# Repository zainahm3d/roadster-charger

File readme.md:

# Roadster Charger
This project is a 65W USB-PD charger for a 36V (nominal) ebike battery. It is designed as a constant current -> constant voltage charger for the Ride1Up Roadster v2 bike.

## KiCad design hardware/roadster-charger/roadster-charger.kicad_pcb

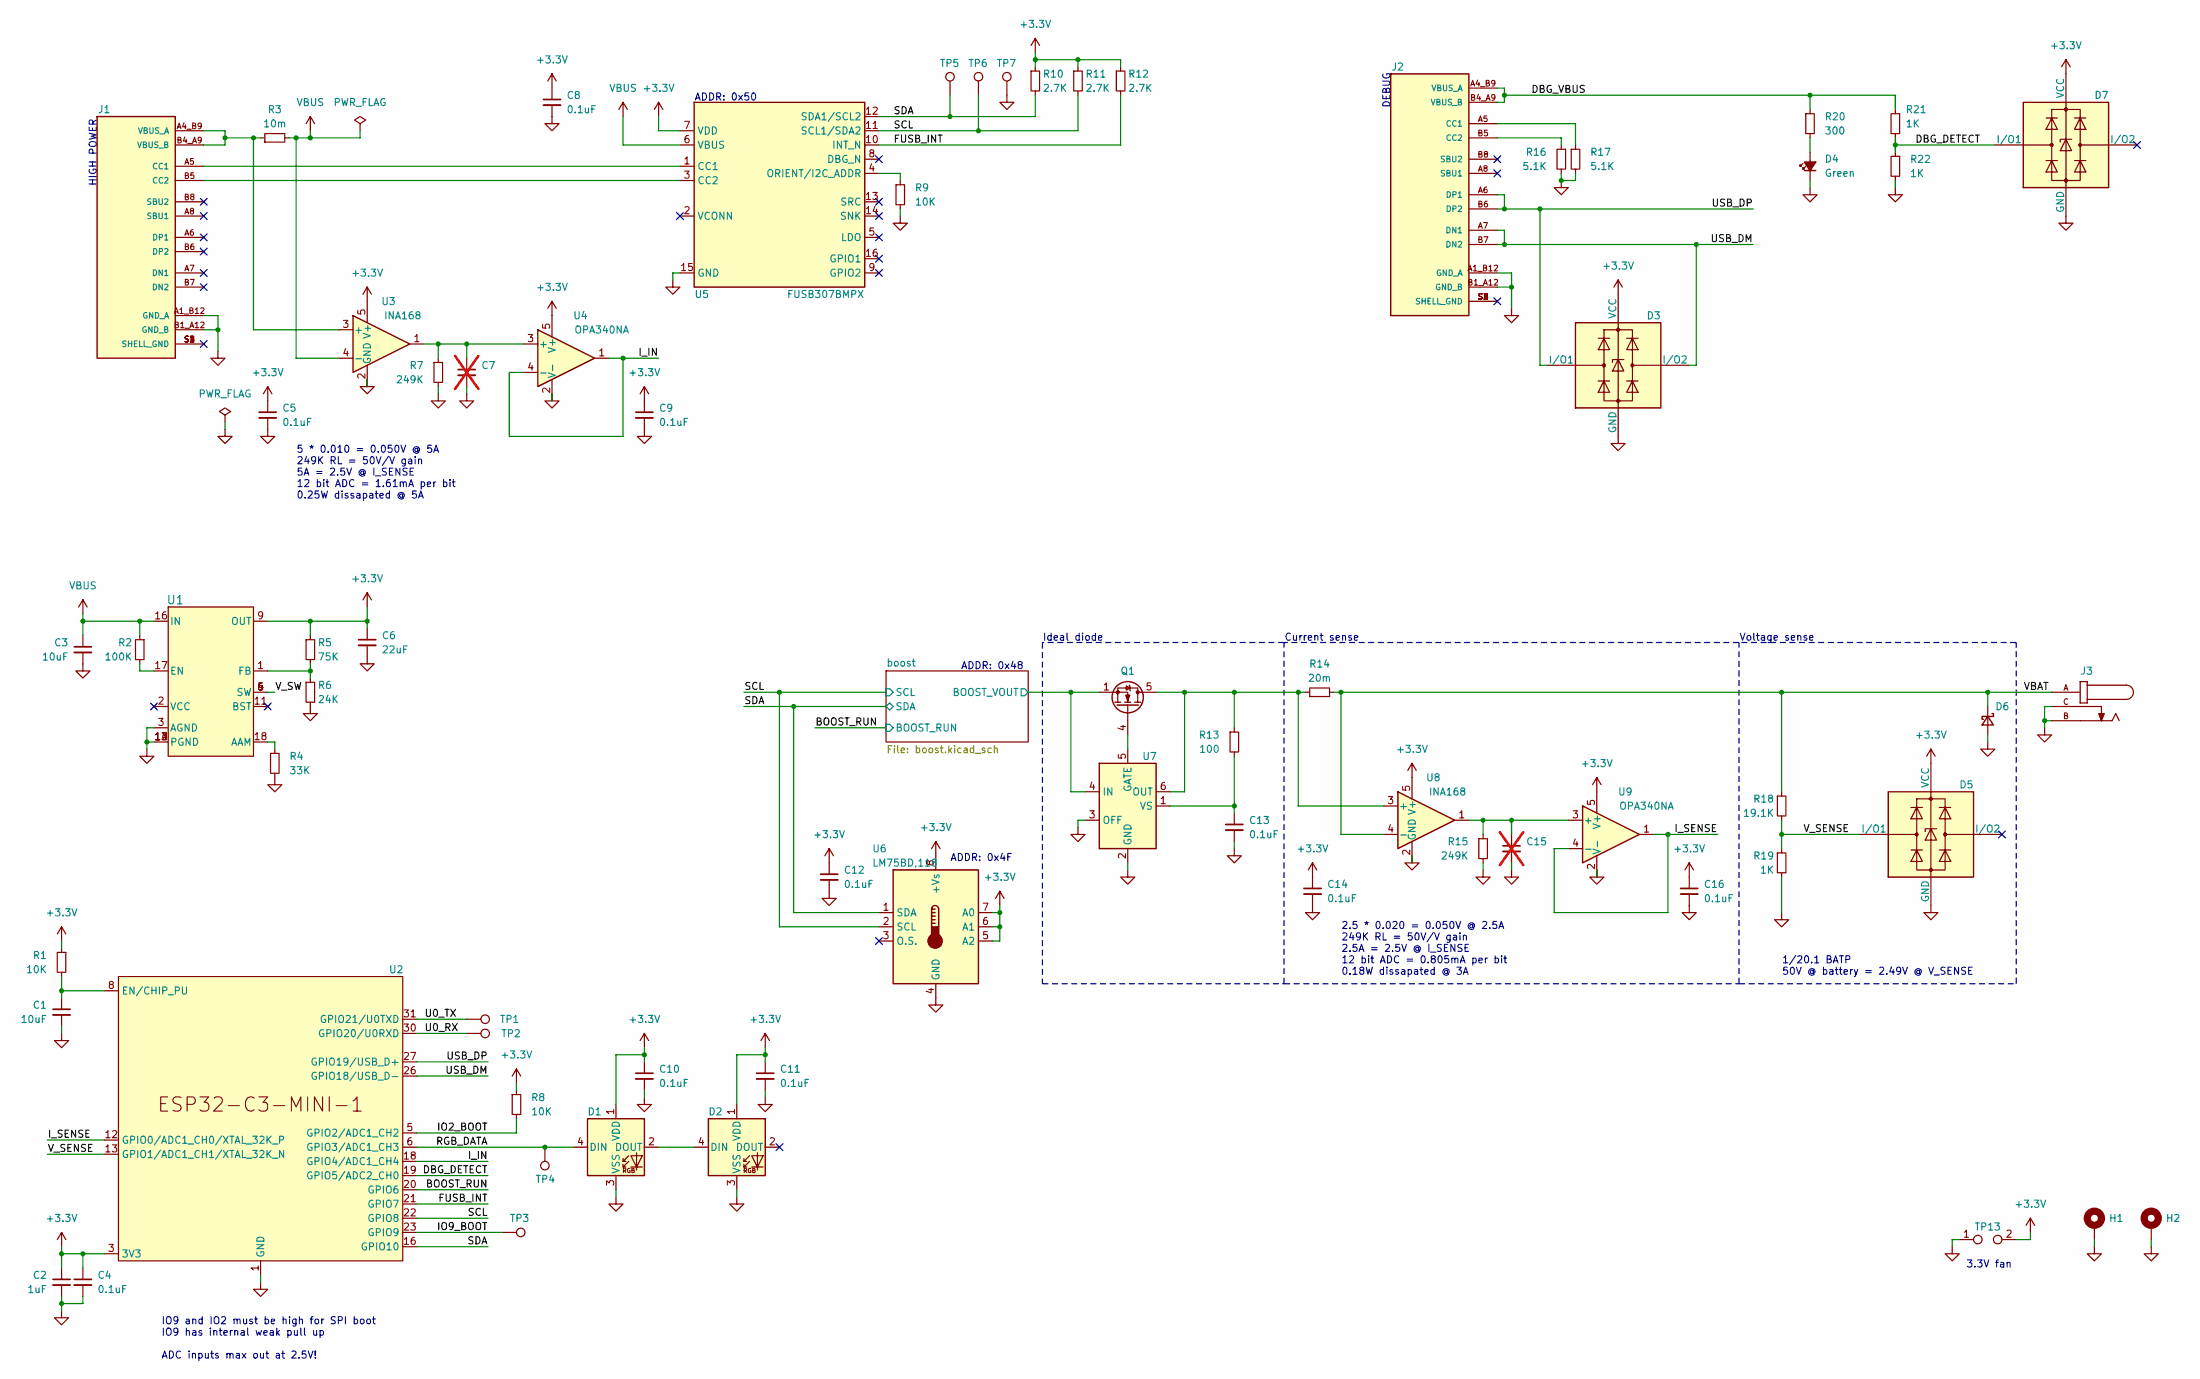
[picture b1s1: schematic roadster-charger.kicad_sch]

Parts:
C1, C3: 10uF; C_1206_3216Metric; MPN CL31A106MBHNNNE
C2: 1uF; C_0805_2012Metric; MPN CL21B105KAFNNNE
C4, C5, C8, C9, C10, C11, C12, C14, C16: 0.1uF; C_0603_1608Metric; MPN CL10B104KB8NNNC
C6: 22uF; C_1206_3216Metric; MPN CL31A226KAHNNNE
C7, C15: C_0603_1608Metric; MPN DNP; not fitted
C13: 0.1uF; C_0603_1608Metric; MPN CL10B104KC8NNNC
D1, D2: WS2812B; LED_WS2812B_PLCC4_5.0x5.0mm_P3.2mm; MPN COM-16347
D3, D5, D7: PRTR5V0U2X; SOT-143; MPN PRTR5V0U2X,215
D4: Green; LED_0805_2012Metric; MPN 150080VS75000
D6: D_Schottky_Small; D_SMB; MPN SMBJ60A
H1, H2: MountingHole_Pad; MountingHole_3.2mm_M3_ISO7380_Pad_TopBottom; MPN DNP
J1, J2: USB4505-03-0-A; GCT_USB4505-03-0-A_REVA; MPN USB4505-03-0-A
J3: 54-00166; TENSILITY_54-00166; MPN 54-00166
Q1: CSD19532Q5B; TDSON-8-1; MPN CSD19532Q5B
R1, R8, R9: 10K; R_0603_1608Metric; MPN RMCF0603FT10K0
R2: 100K; R_0603_1608Metric; MPN RC0603FR-07100KL
R3: 10m; R_1206_3216Metric; MPN PE1206FRF470R01L
R4: 33K; R_0603_1608Metric; MPN RMCF0603FT33K0
R5: 75K; R_0603_1608Metric; MPN RC0603FR-0775KL
R6: 24K; R_0603_1608Metric; MPN RC0603FR-1024KL
R7, R15: 249K; R_0603_1608Metric; MPN RMCF0603FT249K
R10, R11, R12: 2.7K; R_0603_1608Metric; MPN RC0603JR-072K7L
R13: 100; R_0603_1608Metric; MPN RMCF0603FT100R
R14: 20m; R_1206_3216Metric; MPN PA1206FRF470R02L
R16, R17: 5.1K; R_0603_1608Metric; MPN RC0603FR-075K1L
R18: 19.1K; R_0603_1608Metric; MPN RMCF0603FT19K1
R19, R21, R22: 1K; R_0603_1608Metric; MPN RT0603BRD071KL
R20: 300; R_0603_1608Metric; MPN RC0603JR-07330RL
TP1, TP2, TP3, TP4, TP5, TP6, TP7: RCU-0C; TP+195X110; MPN RCU-0C
TP13: TestPoint_2Pads_Pitch2.54mm_Drill0.8mm
U1: MPM3606AGQV-P; QFN3p0x5p0x1p6_MPM3606A_MNP; MPN MPM3606AGQV-P
U2: ESP32-C3-MINI-1; MPN ESP32-C3-MINI-1-N4
U3, U8: INA168; SOT-23-5; MPN INA168NA
U4, U9: OPA340NA; SOT-23-5; MPN OPA340NA
U5: FUSB307BMPX; WQFN-16-1EP_3x3mm_P0.5mm_EP1.75x1.75mm; MPN FUSB307BMPX
U6: LM75BD,118; SOIC-8_3.9x4.9mm_P1.27mm; MPN LM75BD,118
U7: LM5050-1; TSOT-23-6; MPN LM5050MKX-1/NOPB

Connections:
+3.3V: C2.1, C4.1, C5.1, C6.1, C8.1, C9.1, C10.1, C11.1, C12.1, C14.1, C16.1, D1.1 (VDD), D2.1 (VDD), D3.4 (VCC), D5.4 (VCC), D7.4 (VCC), R1.1, R5.1, R8.1, R10.1, R11.1, R12.1, TP13.2, U1.7 (OUT), U1.8 (OUT), U1.9 (OUT), U2.3 (3V3), U3.5 (V+), U4.5 (V+), U5.7 (VDD), U6.5 (A2), U6.6 (A1), U6.7 (A0), U6.8 (+Vs), U8.5 (V+), U9.5 (V+); also elsewhere on the board
/BOOST_RUN: U2.20 (GPIO6); also elsewhere on the board
/DBG_DETECT: D7.2 (I/O1), R21.2, R22.1, U2.19 (GPIO5/ADC2_CH0)
/DBG_VBUS: J2.A4_B9 (VBUS_A), J2.B4_A9 (VBUS_B), R20.1, R21.1
/FUSB_INT: R12.2, U2.21 (GPIO7), U5.10 (INT_N)
/IO2_BOOT: R8.2, U2.5 (GPIO2/ADC1_CH2)
/IO9_BOOT: TP3.1, U2.23 (GPIO9)
/I_IN: U2.18 (GPIO4/ADC1_CH4), U4.1, U4.4 (-)
/I_SENSE: U2.12 (GPIO0/ADC1_CH0/XTAL_32K_P), U9.1, U9.4 (-)
/RGB_DATA: D1.4 (DIN), TP4.1, U2.6 (GPIO3/ADC1_CH3)
/SCL: R11.2, TP6.1, U2.22 (GPIO8), U5.11 (SCL1/SDA2), U6.2 (SCL); also elsewhere on the board
/SDA: R10.2, TP5.1, U2.16 (GPIO10), U5.12 (SDA1/SCL2), U6.1 (SDA); also elsewhere on the board
/U0_RX: TP2.1, U2.30 (GPIO20/U0RXD)
/U0_TX: TP1.1, U2.31 (GPIO21/U0TXD)
/USB_DM: D3.3 (I/O2), J2.A7 (DN1), J2.B7 (DN2), U2.26 (GPIO18/USB_D-)
/USB_DP: D3.2 (I/O1), J2.A6 (DP1), J2.B6 (DP2), U2.27 (GPIO19/USB_D+)
/VBAT: D6.1 (K), J3.A, R14.2, R18.1, U8.4 (-)
/V_SENSE: D5.2 (I/O1), R18.2, R19.1, U2.13 (GPIO1/ADC1_CH1/XTAL_32K_N)
/V_SW: U1.4 (SW), U1.5 (SW), U1.6 (SW)
/boost/BOOST_VOUT: Q1.1 (S), Q1.2 (S), Q1.3 (S), U7.4 (IN); also elsewhere on the board
GND: C1.2, C2.2, C3.2, C4.2, C5.2, C6.2, C7.2, C8.2, C9.2, C10.2, C11.2, C12.2, C13.2, C14.2, C15.2, C16.2, D1.3 (VSS), D2.3 (VSS), D3.1 (GND), D4.1 (K), D5.1 (GND), D6.2 (A), D7.1 (GND), H1.1, H2.1, J1.A1_B12 (GND_A), J1.B1_A12 (GND_B), J2.A1_B12 (GND_A), J2.B1_A12 (GND_B), J3.B, J3.C, R4.2, R6.2, R7.2, R9.2, R15.2, R16.2, R17.2, R19.2, R22.2, TP7.1, TP13.1, U1.3 (AGND), U1.12 (PGND), U1.13 (PGND), U1.14 (PGND), U2.1 (GND), U2.2 (GND), U2.11 (GND), U2.14 (GND), U2.36 (GND), U2.37 (GND), U2.38 (GND), U2.39 (GND), U2.40 (GND), U2.41 (GND), U2.42 (GND), U2.43 (GND), U2.44 (GND), U2.45 (GND), U2.46 (GND), U2.47 (GND), U2.48 (GND), U2.49 (GND), U2.50 (GND), U2.51 (GND), U2.52 (GND), U2.53 (GND), U3.2 (GND), U4.2 (V-), U5.15 (GND), U5.17 (GND), U6.4 (GND), U7.2 (GND), U7.3 (OFF), U8.2 (GND), U9.2 (V-); also elsewhere on the board
unnamed: D1.2 (DOUT), D2.4 (DIN)
unnamed: D4.2 (A), R20.2
unnamed: J1.A5 (CC1), U5.1 (CC1)
unnamed: J1.B5 (CC2), U5.3 (CC2)
unnamed: J1.A4_B9 (VBUS_A), J1.B4_A9 (VBUS_B), R3.1, U3.3 (+)
unnamed: J2.A5 (CC1), R17.1
unnamed: J2.B5 (CC2), R16.1
unnamed: Q1.5 (D), R13.1, R14.1, U7.6 (OUT), U8.3 (+)
unnamed: Q1.4 (G), U7.5 (GATE)
unnamed: R4.1, U1.18 (AAM)
unnamed: R2.2, U1.17 (EN)
unnamed: R5.2, R6.1, U1.1 (FB)
unnamed: C1.1, R1.2, U2.8 (EN/CHIP_PU)
unnamed: C7.1, R7.1, U3.1, U4.3 (+)
unnamed: R9.1, U5.4 (ORIENT/I2C_ADDR)
unnamed: C13.1, R13.2, U7.1 (VS)
unnamed: C15.1, R15.1, U8.1, U9.3 (+)
VBUS: C3.1, R2.1, R3.2, U1.16 (IN), U3.4 (-), U5.6 (VBUS); also elsewhere on the board

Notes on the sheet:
ADDR: 0x50
5 * 0.010 = 0.050V @ 5A 249K RL = 50V/V gain 5A = 2.5V @ I_SENSE 12 bit ADC = 1.61mA per bit 0.25W dissapated @ 5A
3.3V fan
Ideal diode
1/20.1 BATP 50V @ battery = 2.49V @ V_SENSE
DEBUG
HIGH POWER
Current sense
IO9 and IO2 must be high for SPI boot IO9 has internal weak pull up ADC inputs max out at 2.5V!
ADDR: 0x48
ADDR: 0x4F
Voltage sense
2.5 * 0.020 = 0.050V @ 2.5A 249K RL = 50V/V gain 2.5A = 2.5V @ I_SENSE 12 bit ADC = 0.805mA per bit 0.18W dissapated @ 3A

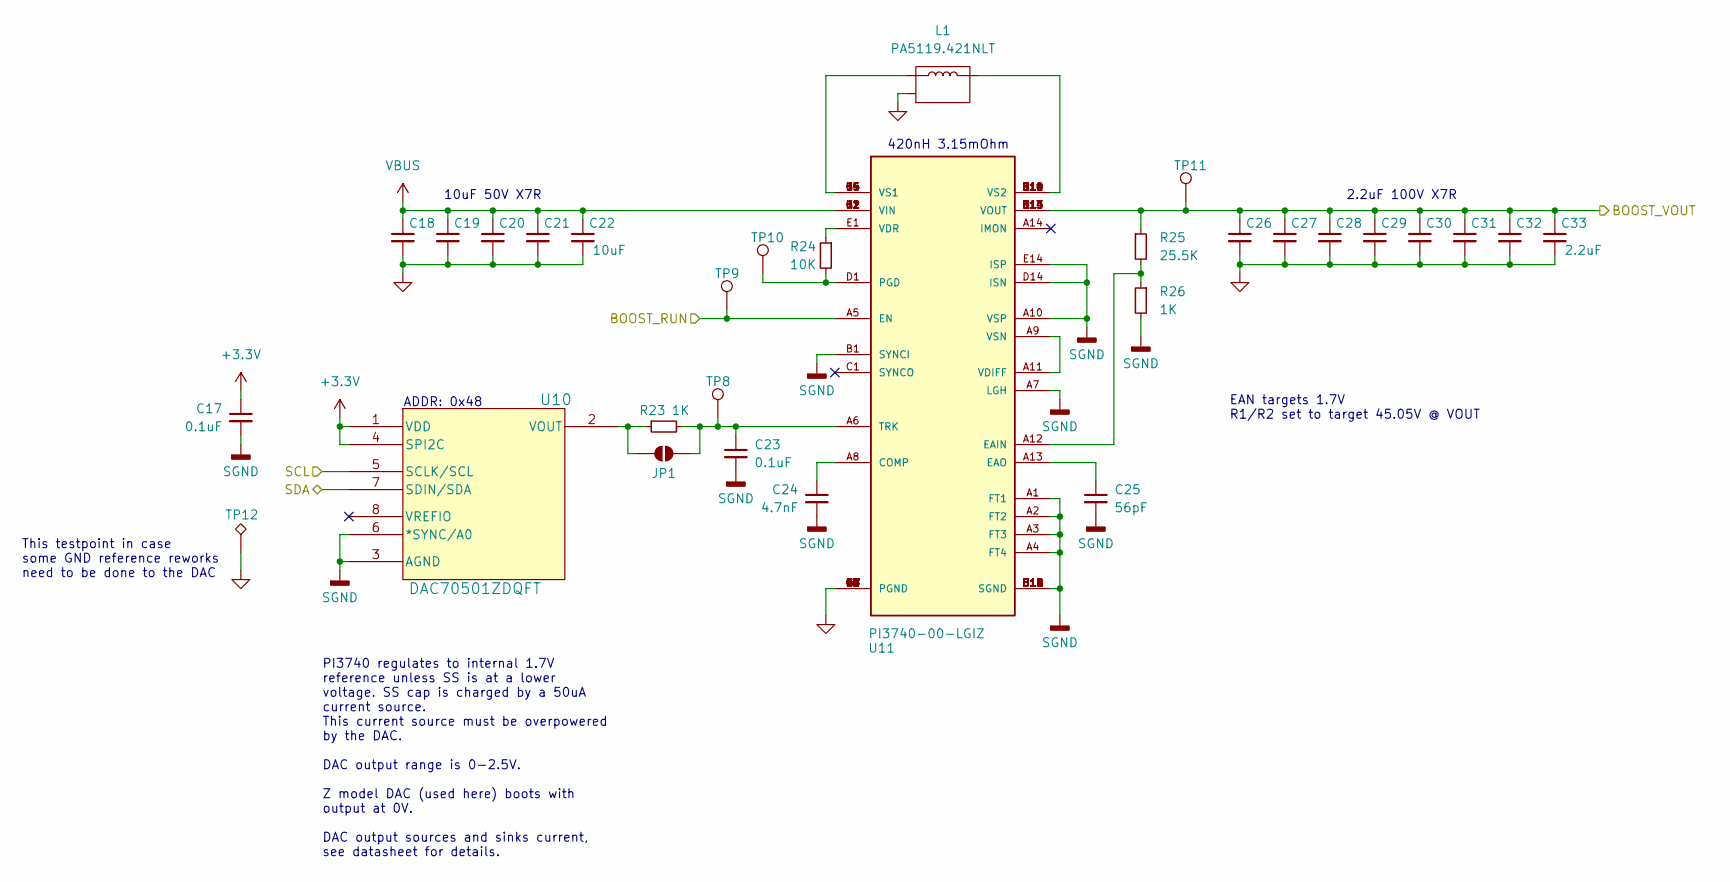
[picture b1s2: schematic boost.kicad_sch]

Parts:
C17, C23: 0.1uF; C_0603_1608Metric; MPN CL10B104KB8NNNC
C18, C19, C20, C21, C22: 10uF; C_1210_3225Metric; MPN CL32B106KBVVPLE
C24: 4.7nF; C_0603_1608Metric; MPN C0603C472K4RECAUTO7411
C25: 56pF; C_0603_1608Metric; MPN C0603C560G5GAC7867
C26, C27, C28, C29, C30, C31, C32, C33: 2.2uF; C_1210_3225Metric; MPN GRM32ER72A225KA35L
JP1: SolderJumper_2_Open; SolderJumper-2_P1.3mm_Open_RoundedPad1.0x1.5mm; MPN DNP
L1: PA5119.421NLT; SMT_119.421NLT_PUL; MPN PA5119.421NLT
R23, R26: 1K; R_0603_1608Metric; MPN RT0603BRD071KL
R24: 10K; R_0603_1608Metric; MPN RMCF0603FT10K0
R25: 25.5K; R_0603_1608Metric; MPN RT0603BRD0725K5L
TP8, TP9, TP10, TP11: RCU-0C; TP+195X110; MPN RCU-0C
TP12: TestPoint_Alt; TestPoint_THTPad_D1.0mm_Drill0.5mm; MPN DNP
U10: DAC70501ZDQFT; WSON8_2P1X2P1_TEX; MPN DAC70501ZDQFT
U11: PI3740-00-LGIZ; LGA108S100P10X14_1000X1400X263N; MPN PI3740-00-LGIZ

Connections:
+3.3V: C17.1, U10.1 (VDD), U10.4 (SPI2C); also elsewhere on the board
/BOOST_RUN: TP9.1, U11.A5 (EN); also elsewhere on the board
/SCL: U10.5 (SCLK/SCL); also elsewhere on the board
/SDA: U10.7 (SDIN/SDA); also elsewhere on the board
/boost/BOOST_VOUT: C26.1, C27.1, C28.1, C29.1, C30.1, C31.1, C32.1, C33.1, R25.1, TP11.1, U11.G13 (VOUT), U11.G14 (VOUT), U11.H13 (VOUT), U11.H14 (VOUT), U11.J13 (VOUT), U11.J14 (VOUT), U11.K13 (VOUT), U11.K14 (VOUT); also elsewhere on the board
GND: C18.2, C19.2, C20.2, C21.2, C22.2, C26.2, C27.2, C28.2, C29.2, C30.2, C31.2, C32.2, C33.2, L1.3 (MNT), TP12.1, U11.B2 (PGND), U11.B3 (PGND), U11.B4 (PGND), U11.B5 (PGND), U11.B6 (PGND), U11.B7 (PGND), U11.B8 (PGND), U11.B9 (PGND), U11.C2 (PGND), U11.C3 (PGND), U11.C4 (PGND), U11.C5 (PGND), U11.C6 (PGND), U11.C7 (PGND), U11.C8 (PGND), U11.C9 (PGND), U11.D2 (PGND), U11.D3 (PGND), U11.D4 (PGND), U11.D5 (PGND), U11.D6 (PGND), U11.D7 (PGND), U11.D8 (PGND), U11.D9 (PGND), U11.E2 (PGND), U11.E3 (PGND), U11.E4 (PGND), U11.E5 (PGND), U11.E6 (PGND), U11.E7 (PGND), U11.E8 (PGND), U11.E9 (PGND), U11.F7 (PGND), U11.F8 (PGND), U11.G7 (PGND), U11.G8 (PGND), U11.H7 (PGND), U11.H8 (PGND), U11.J7 (PGND), U11.J8 (PGND), U11.K7 (PGND), U11.K8 (PGND); also elsewhere on the board
unnamed: C23.1, JP1.1 (A), R23.2, TP8.1, U11.A6 (TRK)
unnamed: JP1.2 (B), R23.1, U10.2 (VOUT)
unnamed: L1.1, U11.G10 (VS2), U11.G11 (VS2), U11.H10 (VS2), U11.H11 (VS2), U11.J10 (VS2), U11.J11 (VS2), U11.K10 (VS2), U11.K11 (VS2)
unnamed: L1.2, U11.G4 (VS1), U11.G5 (VS1), U11.H4 (VS1), U11.H5 (VS1), U11.J4 (VS1), U11.J5 (VS1), U11.K4 (VS1), U11.K5 (VS1)
unnamed: C24.1, U11.A8 (COMP)
unnamed: R25.2, R26.1, U11.A12 (EAIN)
unnamed: C25.1, U11.A13 (EAO)
unnamed: R24.2, TP10.1, U11.D1 (PGD)
unnamed: U11.A9 (VSN), U11.A11 (VDIFF)
unnamed: R24.1, U11.E1 (VDR)
SGND: C17.2, C23.2, C24.2, C25.2, R26.2, U10.3 (AGND), U10.6 (*SYNC/A0), U11.A1 (FT1), U11.A2 (FT2), U11.A3 (FT3), U11.A4 (FT4), U11.A7 (LGH), U11.A10 (VSP), U11.B1 (SYNCI), U11.B10 (SGND), U11.B11 (SGND), U11.B12 (SGND), U11.B13 (SGND), U11.B14 (SGND), U11.C10 (SGND), U11.C11 (SGND), U11.C12 (SGND), U11.D10 (SGND), U11.D11 (SGND), U11.D12 (SGND), U11.D14 (ISN), U11.E10 (SGND), U11.E11 (SGND), U11.E12 (SGND), U11.E14 (ISP)
VBUS: C18.1, C19.1, C20.1, C21.1, C22.1, U11.G1 (VIN), U11.G2 (VIN), U11.H1 (VIN), U11.H2 (VIN), U11.J1 (VIN), U11.J2 (VIN), U11.K1 (VIN), U11.K2 (VIN); also elsewhere on the board

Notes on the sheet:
EAN targets 1.7V R1/R2 set to target 45.05V @ VOUT
ADDR: 0x48
This testpoint in case some GND reference reworks need to be done to the DAC
2.2uF 100V X7R
10uF 50V X7R
420nH 3.15mOhm
PI3740 regulates to internal 1.7V reference unless SS is at a lower voltage. SS cap is charged by a 50uA current source. This current source must be overpowered by the DAC. DAC output range is 0-2.5V. Z model DAC (used here) boots with output at 0V. DAC output sources and sinks current, see datashe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

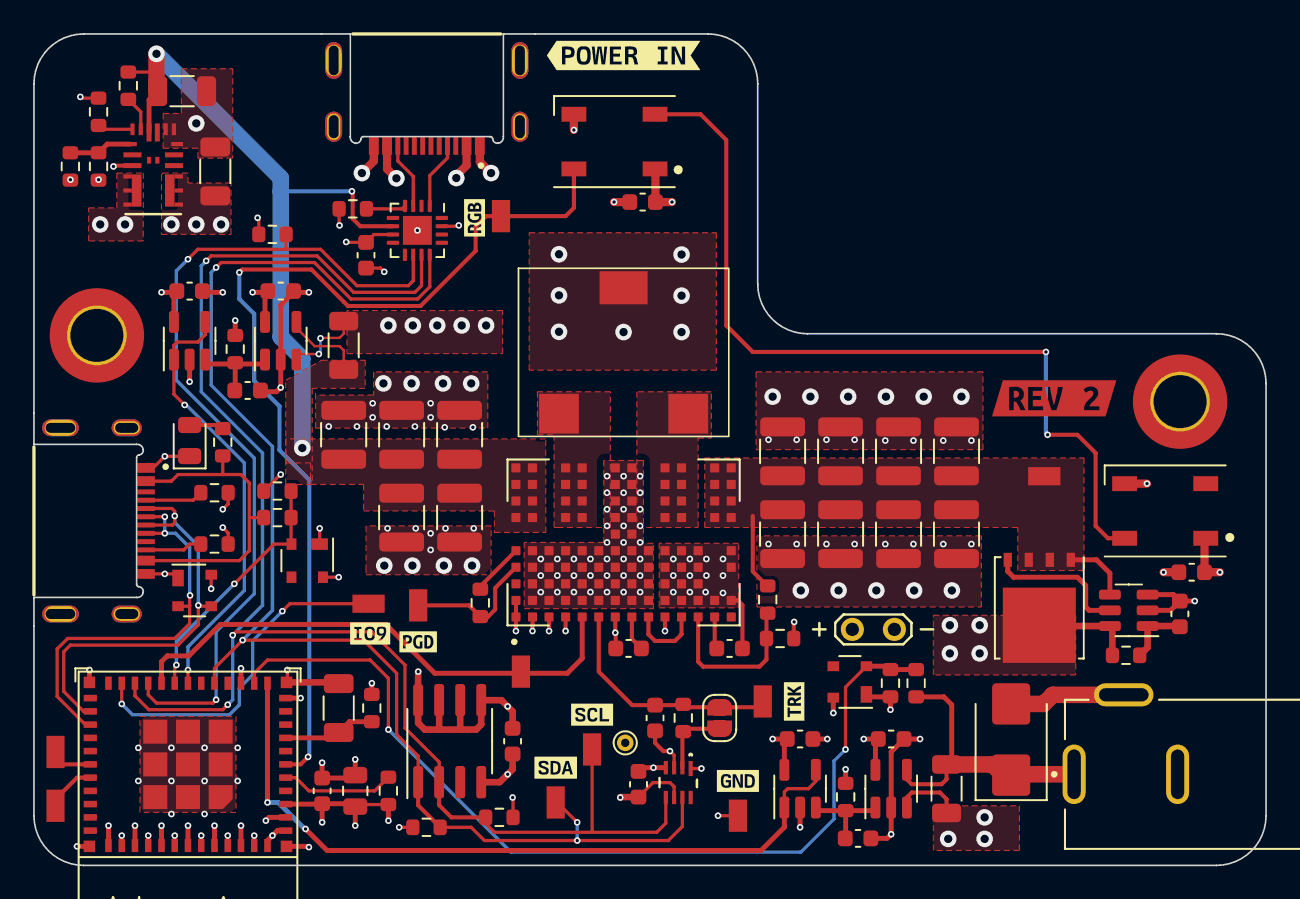
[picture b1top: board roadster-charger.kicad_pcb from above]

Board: 4 copper layers, 74.4 x 50.2 mm, 108 parts (0 on the bottom side), 50 nets.

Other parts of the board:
kibuzzard-657BAFF1: G***; kibuzzard-657BAFF1
kibuzzard-657BAFFB: G***; kibuzzard-657BAFFB
kibuzzard-657BB0E9: G***; kibuzzard-657BB0E9
kibuzzard-657BB005: G***; kibuzzard-657BB005
kibuzzard-657FB5DD: G***; kibuzzard-657FB5DD
kibuzzard-671EA982: G***; kibuzzard-671EA982
kibuzzard-671EA992: G***; kibuzzard-671EA992
kibuzzard-671EAE84: G***; kibuzzard-671EAE84
kibuzzard-671EB1B0: G***; kibuzzard-671EB1B0
kibuzzard-67218F63: G***; kibuzzard-67218F63

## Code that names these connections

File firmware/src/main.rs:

#![no_std]
#![no_main]

use core::sync::atomic::Ordering;
use esp_backtrace as _;
use esp_hal::{
    analog::adc::*,
    delay::Delay,
    gpio::{self, Input, InputConfig, Level, Output, OutputConfig},
    i2c, rtc_cntl,
    time::{Duration, Rate},
    timer::{
        timg::{MwdtStage, MwdtStageAction, TimerGroup, Wdt},
        PeriodicTimer,
    },
    Blocking,
};
use esp_println::println;

esp_bootloader_esp_idf::esp_app_desc!();

use crate::led::color;
mod boost;
mod charger;
mod led;
mod tcpc;
mod temp_sense;
mod usb_pd;
mod vi_sense;

#[rtic::app(device = esp32c3, dispatchers=[FROM_CPU_INTR0, FROM_CPU_INTR1])]
mod app {
    use crate::vi_sense::VISense;

    use super::*;

    #[shared]
    struct Shared {
        i2c: i2c::master::I2c<'static, Blocking>,
    }

    #[local]
    struct Local {
        fusb_int: gpio::Input<'static>,
        periodic: PeriodicTimer<'static, Blocking>,
        boost_enable: gpio::Output<'static>,
        vi_sense: VISense,
        state: shared::state::State,
        leds: led::Led,
        watchdog: Wdt<esp_hal::peripherals::TIMG0<'static>>,
    }

    #[init]
    fn init(_: init::Context) -> (Shared, Local) {
        let peripherals = esp_hal::init(esp_hal::Config::default());
        let mut delay = Delay::new();

        let i2c_config = i2c::master::Config::default().with_frequency(Rate::from_khz(400));
        let mut i2c = i2c::master::I2c::new(peripherals.I2C0, i2c_config)
            .unwrap()
            .with_scl(peripherals.GPIO8)
            .with_sda(peripherals.GPIO10);

        let rmt = esp_hal::rmt::Rmt::new(peripherals.RMT, Rate::from_mhz(80)).unwrap();
        let rmt_output = Output::new(peripherals.GPIO3, Level::Low, Default::default());
        let mut leds = led::Led {
            pixel_buffer: [led::Rgb { r: 0, g: 0, b: 0 }; 2],
            rmt_channel: Some(led::Led::configure_rmt(rmt, rmt_output)),
            last_update_time: esp_hal::time::Instant::EPOCH,
        };

        let mut adc1_config = AdcConfig::new();
        let vi_sense = VISense {
            v_sense: adc1_config.enable_pin_with_cal(peripherals.GPIO1, Attenuation::_11dB),
            i_sense: adc1_config.enable_pin_with_cal(peripherals.GPIO0, Attenuation::_11dB),
            input_i_sense: adc1_config.enable_pin_with_cal(peripherals.GPIO4, Attenuation::_11dB),
            adc: Adc::new(peripherals.ADC1, adc1_config),
            input_current_ma: 0,
            output_current_ma: 0,
            battery_voltage_mv: 0,
        };

        let mut boost_enable = Output::new(peripherals.GPIO6, Level::Low, OutputConfig::default());
        let mut fusb_int = Input::new(peripherals.GPIO7, InputConfig::default());

        boost::init(&mut i2c, &mut boost_enable);
        tcpc::init(&mut i2c, &mut delay);

        let reset_reason = rtc_cntl::reset_reason(esp_hal::system::Cpu::ProCpu);
        if let Some(reason) = reset_reason {
            if reason == rtc_cntl::SocResetReason::CoreMwdt0 {
                println!("System reset was due to watchdog");
                leds.set_pixel(0, color::PURPLE);
                leds.set_pixel(1, color::PURPLE);

                #[allow(clippy::empty_loop)]
                loop {}
            }
        }

        if tcpc::establish_pd_contract(&mut i2c, &mut fusb_int, &mut delay) {
            leds.set_pixel(0, color::GREEN);
        } else {
            leds.set_pixel(0, color::RED);
            panic!("failed to establish PD contract");
        }
        leds.set_pixel(1, color::RED);

        let timg0 = TimerGroup::new(peripherals.TIMG0);
        let mut watchdog = timg0.wdt;
        watchdog.set_stage_action(MwdtStage::Stage3, MwdtStageAction::ResetSystem);
        watchdog.set_timeout(MwdtStage::Stage3, Duration::from_secs(2));
        watchdog.enable();

        let mut periodic = PeriodicTimer::new(timg0.timer0);
        periodic.enable_interrupt(true);
        periodic
            .start(Duration::from_millis(
                1_000 / charger::TICKS_PER_SECOND as u64,
            ))
            .unwrap();

        let mut state = shared::state::State {
            pdo_mv: tcpc::PDO_VOLTAGE_MV.load(Ordering::Relaxed),
            pdo_ma: tcpc::PDO_CURRENT_MA.load(Ordering::Relaxed),
            ..Default::default()
        };

        charger::init(&mut state); // Set PI gains

        (
            Shared { i2c },
            Local {
                fusb_int,
                periodic,
                boost_enable,
                vi_sense,
                state,
                leds,
                watchdog,
            },
        )
    }

    #[task(binds=GPIO, local=[fusb_int], shared=[i2c], priority=1)]
    fn gpio_handler(mut c: gpio_handler::Context) {
        if c.local.fusb_int.is_low() {
            c.local.fusb_int.clear_interrupt();
            c.shared.i2c.lock(|i2c| {
                tcpc::write_reg(i2c, tcpc::Register::AlertL, &0xFF);
            });
        }
    }

    // Update control values and read back sensors
    #[ task(binds=TG0_T0_LEVEL,
        local=[periodic, boost_enable, vi_sense, state, leds, watchdog],
        shared=[i2c], priority=2) ]
    fn timer_handler(mut c: timer_handler::Context) {
        c.local.periodic.clear_interrupt();
        c.local.watchdog.feed();
        c.local.vi_sense.run();
        c.shared.i2c.lock(|i2c| {
            charger::run(
                i2c,
                c.local.boost_enable,
                c.local.state,
                c.local.vi_sense,
                c.local.leds,
            );
        });
    }
}

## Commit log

2023-08-29 init
2023-08-30 rough out boost converter
2023-09-03 add v/i sense, ideal diode, cleanup
2023-09-03 add buffer to I_SENSE
2023-09-04 add readme, swap out lv buck, swap n fets
2023-09-06 schematic cleanup and labeling
2023-09-06 add current sense to VBUS
2023-10-01 cleanup input current sense, assign some footprints
2023-10-01 swapped LTM8074 with cheaper MPM3606A
2023-10-02 fix accidental schem. grid change, add footprints and MPNs
2023-10-02 edit ERC rules, clean up ERC errors, cleanup more off grid parts
2023-10-08 import to PCB, build layout packs
2023-10-09 wip routing
2023-12-03 add LM75 i2c current sensor
2023-12-03 add AAM resistor to 3V3 regulator, validate feedback resistors
2023-12-03 add output transient suppressor
2023-12-10 rough out boost converter again
2023-12-11 continue routing
2023-12-11 correct LED data pin, routing
2023-12-15 cleanup
2023-12-15 move components dir inside of kicad project 🤦‍
2023-12-15 3D models all wired up
2023-12-15 clean up debug USB-C port components
2023-12-16 clear drc issues
2023-12-16 fix off grid ERC issue
2023-12-16 add charger image to back
2023-12-17 add in some missing PNs
2023-12-18 Configure GitHub Actions
2023-12-18 run schematic annotation to clean up error
2023-12-18 clean up fab layer, add value to test points
2023-12-18 add note to DAC circuit, swap DAC to model with 0V output at boot
2023-12-18 add IO9 test point for when I accidentally reassign usb pins during fw dev
2023-12-18 correct schem comments for 2.5V max ADC input
2023-12-18 add additional CI pcb pdf output (fab)
2023-12-18 improve routing for 3.3V regulator
2023-12-18 fix some via sizes
2023-12-18 add doc pdfs and screenshot of board
2023-12-19 move revision label to front cu/front mask
2023-12-20 fix solder mask aperture issue
2023-12-20 Rev 1 PCB (#1)
    * rough out boost converter
    * add v/i sense, ideal diode, cleanup
    * add buffer to I_SENSE
    * add readme, swap out lv buck, swap n fets
    * schematic cleanup and labeling
    * add current sense to VBUS
2023-12-20 change vout voltage divider to target max 2.5V @ 50V at battery
2024-01-04 woo all i2c devices work
2024-01-04 confirm comms with LM75
2024-01-04 confirm comms with fusb307
2024-01-04 test cc line orientation detection
2024-01-05 gross wip test code, goodCRC works!
2024-01-07 disconnect unused CC line rd to allow transmission on CC1 and CC2
2024-01-07 remove look4connection, bump i2c speed to 400k, disable boost now that the hw is good
2024-01-07 DAC and boost work all the way to 48V!
2024-01-08 start filling in FUSB307 bitfields
2024-01-10 bitfields are sick
2024-01-10 create read_reg and write_reg functions
2024-01-11 scaffold out more bitfields
2024-01-12 add header definition
2024-01-12 rename fusb307 to tcpc
2024-01-12 start scaffolding out boost converter control
2024-01-13 wip fusb307 stuff
2024-01-13 WIP board has negotiated PD for the first time
2024-01-14 I am the type c port manager now
2024-01-15 reading in rx buffer
2024-01-16 print out all pdos
2024-01-16 fix off by one error
2024-01-16 delay after fusb307 reset
2024-01-16 rx buffer read figures out rxbytecnt on its own
2024-01-19 bump cpu clock to 160Mhz. Seems to work
2024-01-19 tcpc get_rx_buffer cleanup
2024-01-19 somewhat intelligently select a PDO
2024-01-20 parse out PPS PDOs
2024-01-20 correct DAC full scale voltage
2024-01-20 set up board temperature sensing
2024-01-21 Firmware Bringup + test implementation of PD (#2)
    * woo all i2c devices work
    * confirm comms with LM75
    * confirm comms with fusb307
    * test cc line orientation detection
    * gross wip test code, goodCRC works!
    * disconnect unused CC line rd to allow transmission on CC1 and CC2
2024-01-26 connect FUSB307 vbus pin
2024-01-26 start building out state machine for PD
2024-02-19 continue working on state machine
2024-02-19 add pd negotiation timeout
2024-02-24 update dependencies, todo: update esp32c3 hal
2024-02-24 service post-negotiation PD messages in an interrupt
2024-02-24 run clippy and format documents
2024-02-24 remove boot print
2024-02-26 write ws28128b driver, turn on LEDs for PD status
2024-03-02 allow back to back led updates
2024-03-02 tcpc exposes pdo current and voltage
2024-03-02 increase led inter frame time
2024-05-06 update esp_hal dependency
2024-05-13 bring up ADC
2024-05-27 build a telemetry parser to dump data into influxdb
2024-06-01 print status lines while script is running
2024-06-01 [Very WIP] start building out state machine for charger logic
2024-09-08 Update to KiCad 8 + sneaky resistor PN correction
    Update checkout and artifact actions
    Remove specific board outputs from actions file (kicad bug fixed now)
2024-09-08 update integrating controller
2024-09-09 Build firmware in Actions
2024-09-10 CV charging based on battery voltage
2024-09-11 clippy+rustfmt in CI, correct boost error logic
2024-10-27 Rough rev 2 layout
    Move boost run pin to GPIO6 to avoid hard coded UART output
2024-10-28 add debug connected LED
2024-10-28 change all 1K Rs to 0.1%, invert DAC jumpers
2024-10-30 reannotate, add uart test points
2024-10-30 use track cleanup tool
2024-11-01 Correct Vicor grounding and redo boost layout
2024-11-01 unify zone clearance and width settings
2024-11-02 one more big grounding change
2024-11-03 ERC / DRC cleanup
2024-11-03 Fix res PN, remove TPs from BOM, add DNPs to BOM
2024-11-03 Change bom output to CSV
2024-11-03 Undo DNPs in BOM, update cap PN
2024-11-28 Add capacitor labels
2024-11-28 Bump shunts to 1W 1206 parts
2024-11-28 Move LEDs near input and output ports
2024-12-01 prune bogus symbol fields
2024-12-01 re-add all TPs but TP12 to BOM
2024-12-01 cleanup 3.3V buck pour
2024-12-09 thicken up some power tracks
2024-12-15 connect inductor mounting pin to large ground area
2024-12-21 increase input capacitance for buck / boost
2024-12-21 update all deps except esp-hal
2024-12-22 start the move to RTIC
2024-12-24 add periodic timer and soft reset if we are already connected to a PD source
2024-12-27 clean up USB
2024-12-29 move update logic into timer handler
2024-12-29 Change DAC to output 0-2.5V for new HW
2025-01-13 Correct resistor from 1206 to 0603
2025-01-25 Use generic i2c and digital pins
2025-02-25 bump to kicad 9
2025-03-03 bump to esp-hal 1.0.0
2025-03-08 changes for v2
2025-03-09 redo charger logic
2025-03-09 add a cap discharge period before reenabling disabled charger
2025-03-09 calculate charge current based on connect supply
2025-03-09 get rid of extra variable for max output
2025-03-10 strucify VI_SENSE and LED drivers
2025-03-14 enable watchdog
2025-03-15 Small updates from Rev 2 production run
2025-03-15 limit CV voltage slew rate within 100mV of target
2025-03-16 really need to come up with a decent telemetry format
2025-03-18 add fan connection points
2025-04-18 add heatsink render
2025-04-28 Add overtemp detection, reduce charge current to 1.5A
2025-04-28 Bump i2c to 400khz
2025-04-28 Clippy suggestions
2025-04-28 Clean up disabling logic, add ramp state
2025-06-20 re add min battery voltage check
2025-06-20 Add probe-rs debugger config
2025-06-20 Remove devcontainer and unused scripts
2025-06-20 update telemetry to read new struct
2025-06-20 start adding rerun.io viewer
2025-06-21 Set minimum charge current to cutoff current
2025-06-23 Variableify tick rate, add another overvolt check
2025-10-28 Update to esp_hal rc1
2025-10-31 Panic when timer ISR fires
2025-11-02 Add in a PI controller
2025-11-03 Log telemetry via zerocopy bitstream
2025-11-10 Multiply telmetry packets to allow rerun to plot @ 100FPS
2025-11-11 Undo telemetry packet multiplier
2025-11-11 Run charging loop at 100hz, add 5mA CC deadband
2025-11-22 Log more scalars to rerun
2025-11-27 Log charger control mode
2025-11-28 Update charger logic based on testing
2026-01-04 Un-nest current controller
